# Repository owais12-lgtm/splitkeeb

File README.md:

This my 42 key wireless split keyboard! It follows the corne layout I believe with a 3x6+3 layout. It will use 42 switches and a screen, and is powered by a custom made rp2040 dev board.

# pictures 

# Features
- Dual-core M0+ processor
- Flexible clock running up to 133 MHz
- 264 kB of SRAM
- USB 1.1 controller and PHY with device and host support
- Low-power sleep and dormant modes
- Accurate clock and timer
- Accelerated floating-point libraries
- Temperature sensor
- Oled screen

# BOM 

| Name | Purpose | Quantity | Total Cost (USD) | Link | Distributor |
|------|---------|----------|-----------------|------|-------------|
| PCB | PCB | 1 | $60.00 | [lioncircuits.com](https://www.lioncircuits.com/quote) | Lion Circuits |
| Keycaps | Keycaps | 1 | $30.00 | [curiositycaps.in](https://curiositycaps.in/products/polar-day-line-crack-side-backlit-cherry-keycaps) | Curiosity Caps |
| Akko V3 Silver | Switches | 2 | $32.00 | [stackskb.com](https://stackskb.com/store/akko-v3-silver-pro-switch-pack-of-45/) | StacksKB |
| OLED | OLED | 1 | $2.00 | [robu.in](https://robu.in/product/0-91-inch-128x32-i2c-iic-serial-blue-oled-lcd-display-module/) | Robu |

# CAD
https://www.tinkercad.com/things/a4B1lVT00vB-epic-allis-leelo?sharecode=KdJOAqElzg50q9dy6yfUfhPSDzxFtZ2tY2mduqYmmd4

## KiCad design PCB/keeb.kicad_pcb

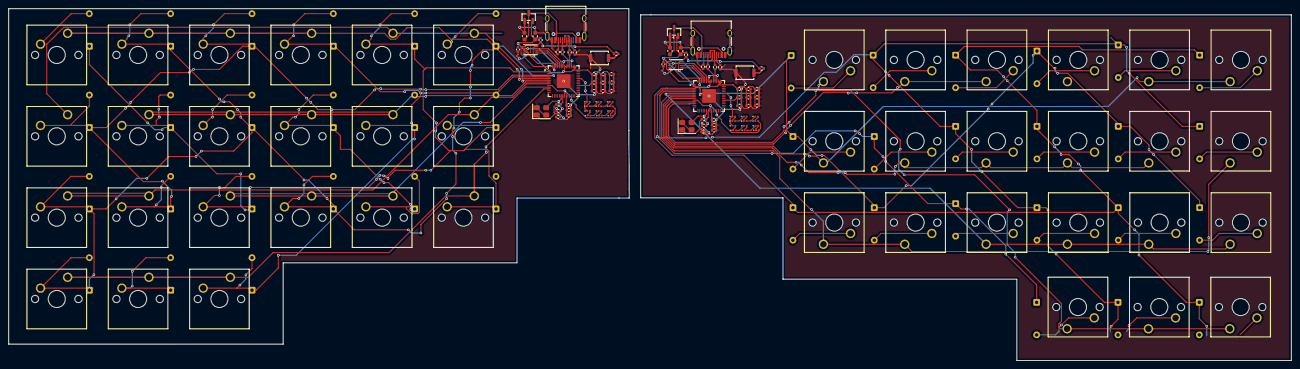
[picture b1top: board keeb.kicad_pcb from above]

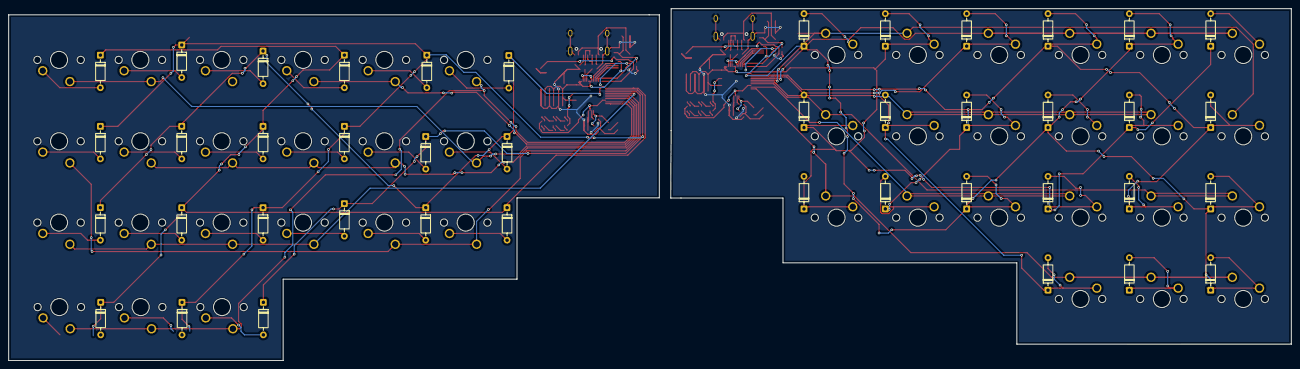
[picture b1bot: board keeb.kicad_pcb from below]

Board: 2 copper layers, 300.4 x 82.4 mm, 168 parts (42 on the bottom side), 103 nets.

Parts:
C1, C1#2, C4, C4#2: 1uF; C_0402_1005Metric
C2, C2#2, C3, C3#2, C5, C5#2, C6, C6#2, C7, C7#2, C8, C8#2, C9, C9#2, C10, C10#2, C11, C11#2, C12, C12#2, C17, C17#2: 0.1uF; C_0402_1005Metric
C13, C13#2, C14, C14#2: 33pF; C_0402_1005Metric
C15, C15#2, C16, C16#2: 10uF; C_0603_1608Metric
D1, D2, D3, D4, D5, D6, D7, D8, D9, D10, D11, D12, D13, D14, D15, D16, D17, D18, D19, D20, D21, D34, D35, D36, D37, D38, D39, D40, D41, D42, D43, D44, D45, D46, D47, D48, D49, D50, D51, D52, D53, D54: 1N4148; D_DO-35_SOD27_P7.62mm_Horizontal
D22, D22#2, D23, D23#2, D24, D24#2, D25, D25#2, D26, D26#2, D27, D27#2, D28, D28#2, D29, D29#2, D30, D30#2, D31, D31#2, D32, D32#2, D33, D33#2: LED; LED_0201_0603Metric
J1, J1#2: USB_C_Receptacle_USB2.0_14P; USB_C_Receptacle_HRO_TYPE-C-31-M-12
R1, R1#2, R2, R2#2: 27; R_0402_1005Metric
R3, R3#2, R6, R6#2: 1K; R_0402_1005Metric
R4, R4#2, R5, R5#2: 5.1K; R_0402_1005Metric
R7, R7#2: 10K; R_0402_1005Metric
SW1, SW2, SW3, SW4, SW5, SW6, SW7, SW8, SW9, SW10, SW11, SW12, SW13, SW14, SW15, SW16, SW17, SW18, SW19, SW20, SW21, SW23, SW24, SW25, SW26, SW27, SW28, SW29, SW30, SW31, SW32, SW33, SW34, SW35, SW36, SW37, SW38, SW39, SW40, SW41, SW42, SW43: SW_Push_45deg; SW_Cherry_MX_1.00u_PCB
SW22, SW22#2: SW_Push; SW_Push_SPST_NO_Alps_SKRK
U1, U1#2: RP2040; QFN-56-1EP_7x7mm_P0.4mm_EP3.2x3.2mm
U2, U2#2: MCP1700x-330xxTT; SOT-23
U3, U3#2: W25Q16JVUXIQ TR; Winbond_USON-8-1EP_3x2mm_P0.5mm_EP0.2x1.6mm
Y1, Y1#2: 12 MHz; Crystal_SMD_3225-4Pin_3.2x2.5mm

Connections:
+1V1: C1.1, C1#2.1, C2.1, C2#2.1, C3.1, C3#2.1, U1.23 (DVDD), U1.45 (VREG_VOUT), U1.50 (DVDD), U1#2.23 (DVDD), U1#2.45 (VREG_VOUT), U1#2.50 (DVDD)
+3V3: C4.1, C4#2.1, C5.1, C5#2.1, C6.1, C6#2.1, C7.1, C7#2.1, C8.1, C8#2.1, C9.1, C9#2.1, C10.1, C10#2.1, C11.1, C11#2.1, C12.1, C12#2.1, C16.1, C16#2.1, C17.1, C17#2.1, D32.2 (A), D32#2.2 (A), D33.2 (A), D33#2.2 (A), R7.2, R7#2.2, U1.1 (IOVDD), U1.10 (IOVDD), U1.22 (IOVDD), U1.33 (IOVDD), U1.42 (IOVDD), U1.43 (ADC_AVDD), U1.44 (VREG_IN), U1.48 (USB_VDD), U1.49 (IOVDD), U1#2.1 (IOVDD), U1#2.10 (IOVDD), U1#2.22 (IOVDD), U1#2.33 (IOVDD), U1#2.42 (IOVDD), U1#2.43 (ADC_AVDD), U1#2.44 (VREG_IN), U1#2.48 (USB_VDD), U1#2.49 (IOVDD), U2.2 (VO), U2#2.2 (VO), U3.8 (VCC), U3#2.8 (VCC)
Col0: SW1.1, SW2.1, SW3.1, SW4.1, SW23.1, SW24.1, SW25.1, SW26.1, U1.6 (GPIO4), U1#2.6 (GPIO4)
Col1: SW5.1, SW6.1, SW7.1, SW27.1, SW28.1, SW29.1, U1.7 (GPIO5), U1#2.7 (GPIO5)
Col2: SW8.1, SW9.1, SW10.1, SW11.1, SW30.1, SW31.1, SW32.1, SW33.1, U1.8 (GPIO6), U1#2.8 (GPIO6)
Col3: SW12.1, SW13.1, SW14.1, SW34.1, SW35.1, SW36.1, U1.9 (GPIO7), U1#2.9 (GPIO7)
Col4: SW15.1, SW16.1, SW17.1, SW37.1, SW38.1, SW39.1, U1.11 (GPIO8), U1#2.11 (GPIO8)
Col5: SW18.1, SW19.1, SW20.1, SW21.1, SW40.1, SW41.1, SW42.1, SW43.1, U1.12 (GPIO9), U1#2.12 (GPIO9)
GND: C1.2, C1#2.2, C2.2, C2#2.2, C3.2, C3#2.2, C4.2, C4#2.2, C5.2, C5#2.2, C6.2, C6#2.2, C7.2, C7#2.2, C8.2, C8#2.2, C9.2, C9#2.2, C10.2, C10#2.2, C11.2, C11#2.2, C12.2, C12#2.2, C13.1, C13#2.1, C14.1, C14#2.1, C15.2, C15#2.2, C16.2, C16#2.2, C17.2, C17#2.2, J1.A1 (GND), J1.A12 (GND), J1.B1 (GND), J1.B12 (GND), J1.S1 (SHIELD), J1#2.A1 (GND), J1#2.A12 (GND), J1#2.B1 (GND), J1#2.B12 (GND), J1#2.S1 (SHIELD), R4.2, R4#2.2, R5.2, R5#2.2, SW22.1, SW22#2.1, U1.57 (GND), U1#2.57 (GND), U2.1 (GND), U2#2.1 (GND), U3.4 (GND), U3#2.4 (GND), Y1.2, Y1.4, Y1#2.2, Y1#2.4
GPIO11: U1.14 (GPIO11), U1#2.14 (GPIO11)
GPIO12: U1.15 (GPIO12), U1#2.15 (GPIO12)
GPIO13: U1.16 (GPIO13), U1#2.16 (GPIO13)
GPIO14: U1.17 (GPIO14), U1#2.17 (GPIO14)
GPIO15: U1.18 (GPIO15), U1#2.18 (GPIO15)
GPIO16: U1.27 (GPIO16), U1#2.27 (GPIO16)
GPIO17: U1.28 (GPIO17), U1#2.28 (GPIO17)
GPIO18: U1.29 (GPIO18), U1#2.29 (GPIO18)
GPIO19: U1.30 (GPIO19), U1#2.30 (GPIO19)
GPIO20: U1.31 (GPIO20), U1#2.31 (GPIO20)
GPIO21: U1.32 (GPIO21), U1#2.32 (GPIO21)
GPIO22: U1.34 (GPIO22), U1#2.34 (GPIO22)
GPIO23: U1.35 (GPIO23), U1#2.35 (GPIO23)
GPIO24: U1.36 (GPIO24), U1#2.36 (GPIO24)
GPIO26_ADC0: U1.38 (GPIO26_ADC0), U1#2.38 (GPIO26_ADC0)
GPIO27_ADC1: U1.39 (GPIO27_ADC1), U1#2.39 (GPIO27_ADC1)
GPIO28_ADC2: U1.40 (GPIO28_ADC2), U1#2.40 (GPIO28_ADC2)
GPIO29_ADC3: U1.41 (GPIO29_ADC3), U1#2.41 (GPIO29_ADC3)
unnamed: C14.2, C14#2.2, R3.1, R3#2.1, Y1.1, Y1#2.1
unnamed: D1.2 (A), SW1.2
unnamed: D2.2 (A), SW2.2
unnamed: D3.2 (A), SW3.2
unnamed: D4.2 (A), SW4.2
unnamed: D5.2 (A), SW5.2
unnamed: D6.2 (A), SW6.2
unnamed: D7.2 (A), SW7.2
unnamed: D8.2 (A), SW8.2
unnamed: D9.2 (A), SW9.2
unnamed: D10.2 (A), SW10.2
unnamed: D11.2 (A), SW11.2
unnamed: D12.2 (A), SW12.2
unnamed: D13.2 (A), SW13.2
unnamed: D14.2 (A), SW14.2
unnamed: D15.2 (A), SW15.2
unnamed: D16.2 (A), SW16.2
unnamed: D17.2 (A), SW17.2
unnamed: D18.2 (A), SW18.2
unnamed: D19.2 (A), SW19.2
unnamed: D20.2 (A), SW20.2
unnamed: D21.2 (A), SW21.2
unnamed: D22.2 (A), D22#2.2 (A), D24.1 (K), D24#2.1 (K)
unnamed: D22.1 (K), D22#2.1 (K), D23.1 (K), D23#2.1 (K), U1.37 (GPIO25), U1#2.37 (GPIO25)
unnamed: D23.2 (A), D23#2.2 (A), D25.1 (K), D25#2.1 (K)
unnamed: D24.2 (A), D24#2.2 (A), D26.1 (K), D26#2.1 (K)
unnamed: D25.2 (A), D25#2.2 (A), D27.1 (K), D27#2.1 (K)
unnamed: D26.2 (A), D26#2.2 (A), D28.1 (K), D28#2.1 (K)
unnamed: D27.2 (A), D27#2.2 (A), D29.1 (K), D29#2.1 (K)
unnamed: D28.2 (A), D28#2.2 (A), D30.1 (K), D30#2.1 (K)
unnamed: D29.2 (A), D29#2.2 (A), D31.1 (K), D31#2.1 (K)
unnamed: D30.2 (A), D30#2.2 (A), D32.1 (K), D32#2.1 (K)
unnamed: D31.2 (A), D31#2.2 (A), D33.1 (K), D33#2.1 (K)
unnamed: D34.2 (A), SW23.2
unnamed: D35.2 (A), SW24.2
unnamed: D36.2 (A), SW25.2
unnamed: D37.2 (A), SW26.2
unnamed: D38.2 (A), SW27.2
unnamed: D39.2 (A), SW28.2
unnamed: D40.2 (A), SW29.2
unnamed: D41.2 (A), SW30.2
unnamed: D42.2 (A), SW31.2
unnamed: D43.2 (A), SW32.2
unnamed: D44.2 (A), SW33.2
unnamed: D45.2 (A), SW34.2
unnamed: D46.2 (A), SW35.2
unnamed: D47.2 (A), SW36.2
unnamed: D48.2 (A), SW37.2
unnamed: D49.2 (A), SW38.2
unnamed: D50.2 (A), SW39.2
unnamed: D51.2 (A), SW40.2
unnamed: D52.2 (A), SW41.2
unnamed: D53.2 (A), SW42.2
unnamed: D54.2 (A), SW43.2
unnamed: J1.A5 (CC1), J1#2.A5 (CC1), R4.1, R4#2.1
unnamed: J1.B5 (CC2), J1#2.B5 (CC2), R5.1, R5#2.1
unnamed: R6.2, R6#2.2, SW22.2, SW22#2.2
unnamed: R2.2, R2#2.2, U1.46 (USB_DM), U1#2.46 (USB_DM)
unnamed: R1.2, R1#2.2, U1.47 (USB_DP), U1#2.47 (USB_DP)
QSPI_SCLK: U1.52 (QSPI_SCLK), U1#2.52 (QSPI_SCLK), U3.6 (CLK), U3#2.6 (CLK)
QSPI_SD0: U1.53 (QSPI_SD0), U1#2.53 (QSPI_SD0), U3.5 (DI/IO_{0}), U3#2.5 (DI/IO_{0})
QSPI_SD1: U1.55 (QSPI_SD1), U1#2.55 (QSPI_SD1), U3.2 (DO/IO_{1}), U3#2.2 (DO/IO_{1})
QSPI_SD2: U1.54 (QSPI_SD2), U1#2.54 (QSPI_SD2), U3.3 (~WP/IO_{2}), U3#2.3 (~WP/IO_{2})
QSPI_SD3: U1.51 (QSPI_SD3), U1#2.51 (QSPI_SD3), U3.7 (~HOLD/~RESET/IO_{3}), U3#2.7 (~HOLD/~RESET/IO_{3})
QSPI_SS: R6.1, R6#2.1, R7.1, R7#2.1, U1.56 (QSPI_SS), U1#2.56 (QSPI_SS), U3.1 (~CS), U3#2.1 (~CS)
Row0: D1.1 (K), D5.1 (K), D8.1 (K), D12.1 (K), D15.1 (K), D18.1 (K), D34.1 (K), D38.1 (K), D41.1 (K), D45.1 (K), D48.1 (K), D51.1 (K), U1.2 (GPIO0), U1#2.2 (GPIO0)
Row1: D2.1 (K), D6.1 (K), D9.1 (K), D13.1 (K), D16.1 (K), D19.1 (K), D35.1 (K), D39.1 (K), D42.1 (K), D46.1 (K), D49.1 (K), D52.1 (K), U1.3 (GPIO1), U1#2.3 (GPIO1)
Row2: D3.1 (K), D7.1 (K), D10.1 (K), D14.1 (K), D17.1 (K), D20.1 (K), D36.1 (K), D40.1 (K), D43.1 (K), D47.1 (K), D50.1 (K), D53.1 (K), U1.4 (GPIO2), U1#2.4 (GPIO2)
Row3: D4.1 (K), D11.1 (K), D21.1 (K), D37.1 (K), D44.1 (K), D54.1 (K), U1.5 (GPIO3), U1#2.5 (GPIO3)
SWCLK: U1.24 (SWCLK), U1#2.24 (SWCLK)
SWD: U1.25 (SWD), U1#2.25 (SWD)
USB_D+: J1.A6 (D+), J1.B6 (D+), J1#2.A6 (D+), J1#2.B6 (D+), R1.1, R1#2.1
USB_D-: J1.A7 (D-), J1.B7 (D-), J1#2.A7 (D-), J1#2.B7 (D-), R2.1, R2#2.1
VBUS: C15.1, C15#2.1, J1.A4 (VBUS), J1.A9 (VBUS), J1.B4 (VBUS), J1.B9 (VBUS), J1#2.A4 (VBUS), J1#2.A9 (VBUS), J1#2.B4 (VBUS), J1#2.B9 (VBUS), U2.3 (VI), U2#2.3 (VI)
XIN: C13.2, C13#2.2, U1.20 (XIN), U1#2.20 (XIN), Y1.3, Y1#2.3
XOUT: R3.2, R3#2.2, U1.21 (XOUT), U1#2.21 (XOUT)

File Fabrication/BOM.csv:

"Id";"Designator";"Footprint";"Quantity";"Designation";"Supplier and ref";
1;"D33,D27,D26,D28,D24,D30,D32,D31,D23,D29,D25,D22,D29,D23,D30,D33,D24,D26,D27,D25,D32,D31,D28,D22";"LED_0201_0603Metric";24;"LED";;;
2;"C14,C13,C14,C13";"C_0402_1005Metric";4;"33pF";;;
3;"C8,C7,C2,C12,C11,C17,C10,C5,C9,C6,C3,C7,C5,C9,C2,C8,C10,C12,C11,C6,C3,C17";"C_0402_1005Metric";22;"0.1uF";;;
4;"SW29,SW41,SW28,SW39,SW35,SW34,SW40,SW37,SW43,SW27,SW30,SW24,SW33,SW23,SW36,SW38,SW31,SW42,SW25,SW32,SW26,SW8,SW20,SW12,SW19,SW5,SW3,SW18,SW7,SW11,SW14,SW13,SW4,SW21,SW17,SW6,SW2,SW10,SW15,SW16,SW1,SW9";"SW_Cherry_MX_1.00u_PCB";42;"SW_Push_45deg";;;
5;"U2,U2";"SOT-23";2;"MCP1700x-330xxTT";;;
6;"C1,C4,C4,C1";"C_0402_1005Metric";4;"1uF";;;
7;"C16,C15,C16,C15";"C_0603_1608Metric";4;"10uF";;;
8;"R2,R1,R2,R1";"R_0402_1005Metric";4;"27";;;
9;"U1,U1";"QFN-56-1EP_7x7mm_P0.4mm_EP3.2x3.2mm";2;"RP2040";;;
10;"SW22,SW22";"SW_Push_SPST_NO_Alps_SKRK";2;"SW_Push";;;
11;"J1,J1";"USB_C_Receptacle_HRO_TYPE-C-31-M-12";2;"USB_C_Receptacle_USB2.0_14P";;;
12;"R6,R3,R6,R3";"R_0402_1005Metric";4;"1K";;;
13;"R7,R7";"R_0402_1005Metric";2;"10K";;;
14;"R5,R4,R4,R5";"R_0402_1005Metric";4;"5.1K";;;
15;"Y1,Y1";"Crystal_SMD_3225-4Pin_3.2x2.5mm";2;"12 MHz";;;
16;"U3,U3";"Winbond_USON-8-1EP_3x2mm_P0.5mm_EP0.2x1.6mm";2;"W25Q16JVUXIQ TR";;;
17;"D43,D35,D50,D49,D45,D51,D36,D40,D47,D46,D39,D41,D54,D42,D52,D48,D44,D53,D37,D38,D34,D17,D19,D21,D3,D2,D12,D5,D16,D14,D20,D10,D7,D18,D4,D9,D13,D1,D8,D11,D15,D6";"D_DO-35_SOD27_P7.62mm_Horizontal";42;"1N4148";;;
